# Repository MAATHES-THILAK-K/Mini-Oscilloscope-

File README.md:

# **Mini Oscilloscope – Arduino + SH1106 OLED**

A compact oscilloscope built using Arduino, an SH1106 OLED module, and a simple analog front-end.
Includes auto-range, trigger detection, waveform plotting, and frequency/duty-cycle measurement.

> **Reference Project Used:**
> This build was inspired by the project on Instructables:
> *“Build Your Own Arduino Nano Based DIY Oscilloscope”*
> *https://www.instructables.com/Build-Your-Own-Arduino-Nano-Based-DIY-Oscilloscope/*

---

## 🔧 **Features**

* SH1106 128×64 OLED display
* Auto/Manual voltage ranges
* Time-base options from **200 ms/div** to **200 µs/div**
* Trigger detection (rising & falling edge)
* Frequency and duty-cycle calculation
* Average voltage measurement
* EEPROM settings storage
* Battery measurement mode

---

## 📦 **Hardware**

### **Core Components**

* Arduino Nano (ATmega328P)
* SH1106 128×64 I²C OLED display
* Tactile push buttons (4×: SELECT, UP, DOWN, HOLD)
* Voltage divider resistors
* Schottky diode
* 104 capacitor
* Breadboard or custom PCB
* Jumper wires
* 5V regulated power supply

### **Additional Interface Components**

* Input attenuator (1× / 10×)
* User control buttons.

---

## 🧪 **How It Works**

* Samples analog input using ADC with a variable prescaler
* Computes minimum, maximum, and average voltage
* Detects trigger events to stabilize waveform display
* Calculates frequency and duty cycle using edge-cross detection
* Renders waveform using the **Adafruit GFX** library

---

## 🖼 **Photos / Screenshots**

Add images inside the `Images/` folder once your hardware build is ready.

---

## 📁 **Code Structure**

```
MiniOscilloscope/
├── src/
│   └── miniOscilloscope.ino
├── README.md
├── LICENSE
└── Images/
```

---

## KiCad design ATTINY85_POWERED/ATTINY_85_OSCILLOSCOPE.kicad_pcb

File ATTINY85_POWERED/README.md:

# ATtiny85 Powered Mini Oscilloscope – PCB Design

This repository contains the complete PCB design files for a **compact, low-cost mini oscilloscope** powered by the **ATtiny85 microcontroller**.  
The project is intended for **educational, experimental, and embedded systems learning purposes**.

---

## 📷 PCB Preview

---

## 📌 Features

- ATtiny85-based minimal oscilloscope design  
- Compact single-board PCB  
- Designed using **KiCad**
- Low component count for easy fabrication
- Suitable for low-frequency signal visualization
- Ideal for students and hobbyists

---

## 📂 Folder Structure

- **GERBER/** – Manufacturing-ready Gerber files  
- **IMAGES/** – PCB renders and images  
- **3D MODEL/** – 3D visualization of the PCB  
- **BACKUPS/** – Design backups  
- **REPORT/** – Project documentation  
- **POS.zip** – Pick and Place files  
- **\*.kicad_\*** – KiCad project, schematic, and PCB layout files  

---

## 🛠 Tools Used

- KiCad (Schematic & PCB Design)
- ATtiny85 Microcontroller

---

## ⚠️ Disclaimer

This oscilloscope is **not a replacement for professional instruments**.  
It is designed strictly for **learning, experimentation, and demonstration** purposes.

---

## 📜 License

This project is open-source and intended for educational use.  
Feel free to modify and improve the design with proper attribution.

---

### 🚀 Designed & Maintained by  
**MAATHES-THILAK-K**

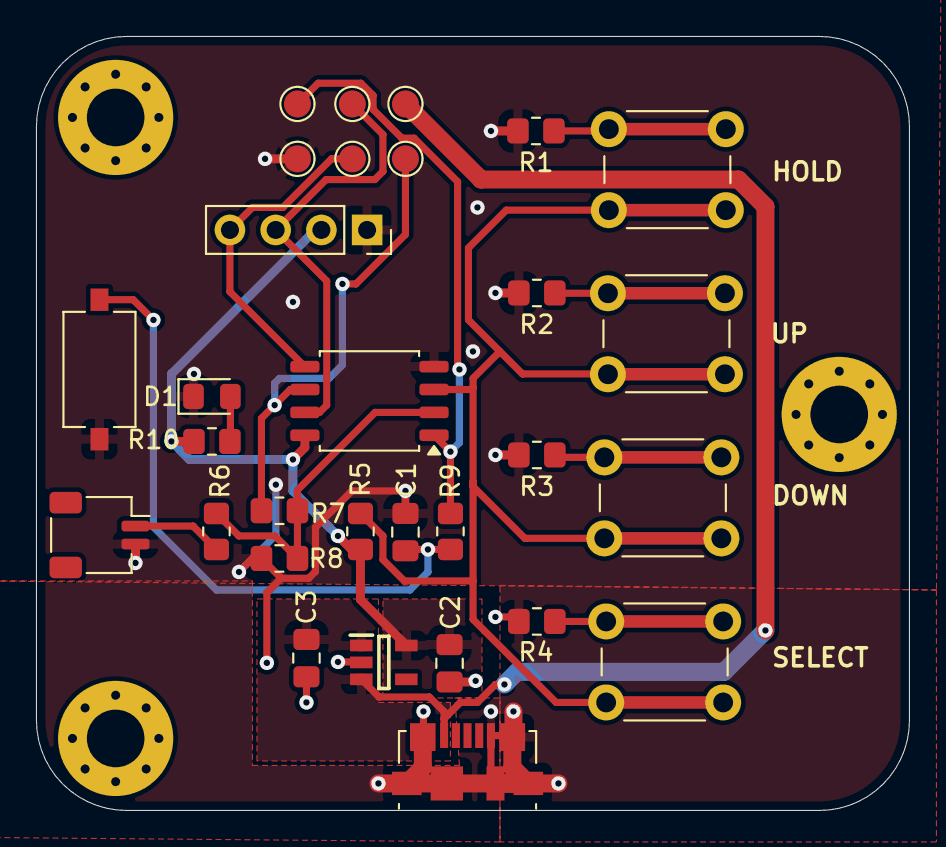
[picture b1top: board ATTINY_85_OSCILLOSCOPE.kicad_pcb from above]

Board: 2 copper layers, 48.5 x 43.0 mm, 33 parts (0 on the bottom side), 16 nets.

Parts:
C1: 100nF; C_0805_2012Metric_Pad1.18x1.45mm_HandSolder
C2, C3: 10uF; C_0805_2012Metric_Pad1.18x1.45mm_HandSolder
D1: LED; LED_0805_2012Metric_Pad1.15x1.40mm_HandSolder
DOWN: SW_SPST; SW_PUSH_6mm
H1, H2, H3: MH; MountingHole_3.2mm_M3_Pad_Via
HOLD: SW_SPST; SW_PUSH_6mm
IC1: RT9080-33GJ5; SOT94P280X100-5N
J1: USB_B_Micro; USB_Micro-B_Molex_47346-0001
J2: 01x02; JST_SH_SM02B-SRSS-TB_1x02-1MP_P1.00mm_Horizontal
J3: 01X04; PinSocket_1x04_P2.54mm_Vertical
R1, R2, R3, R4: 4K7; R_0805_2012Metric_Pad1.20x1.40mm_HandSolder
R5, R9: 10K; R_0805_2012Metric_Pad1.20x1.40mm_HandSolder
R6: 510K; R_0805_2012Metric_Pad1.20x1.40mm_HandSolder
R7: 12K; R_0805_2012Metric_Pad1.20x1.40mm_HandSolder
R8: 120K; R_0805_2012Metric_Pad1.20x1.40mm_HandSolder
R10: 1K; R_0805_2012Metric_Pad1.20x1.40mm_HandSolder
SELECT: SW_SPST; SW_PUSH_6mm
SW5: SW_Push; SW_Tactile_SPST_NO_Straight_CK_PTS636Sx25SMTRLFS
TP1, TP2, TP3, TP4, TP5, TP6: TP; TestPoint_Pad_D1.5mm
U1: ATtiny85-20S; SOIC-8_5.3x5.3mm_P1.27mm
UP: SW_SPST; SW_PUSH_6mm

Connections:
/3V3: C2.1, IC1.5 (VOUT), J3.2, R5.1, R10.1, U1.8 (VCC)
/5V5: C3.1, IC1.1 (VIN), IC1.3 (EN), J1.1 (VBUS), TP5.1
BTN: DOWN.2 (B), HOLD.2 (B), R5.2, SELECT.2 (B), U1.3 (XTAL2/PB4), UP.2 (B)
GND: C1.2, C2.2, C3.2, D1.1 (K), IC1.2 (GND), J1.5 (GND), J1.6 (Shield), J2.2, J3.1, R1.1, R2.1, R3.1, R4.1, R8.2, SW5.2, TP2.1, U1.4 (GND)
IN: R7.1, TP6.1, U1.6 (PB1)
unnamed: C1.1, R9.2, SW5.1
unnamed: D1.2 (A), R10.2
unnamed: HOLD.1 (A), R1.2
unnamed: R2.2, UP.1 (A)
unnamed: DOWN.1 (A), R3.2
unnamed: R4.2, SELECT.1 (A)
RST: R9.1, TP1.1, U1.1 (~RESET/PB5)
SCL: J3.3, TP3.1, U1.7 (PB2)
SDA: J3.4, TP4.1, U1.5 (AREF/PB0)
SGN: R6.2, R7.2, R8.1, U1.2 (XTAL1/PB3)
SGN_IN: J2.1, R6.1

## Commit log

2025-11-24 Create Images
2025-11-24 Create temp
2026-03-20 New code that consumes less SRAM
